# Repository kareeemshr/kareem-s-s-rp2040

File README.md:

# kareem-s-s-rp2040
(small note:there are decoupiling cap's clumped up together cus of space restrictions and no i cant really make the pcb 4 layers because im like 10 bucks away from being over budget)my very own custom devboard that i made...well i made it cus i thought itd be cool as hell and it is,im very proud of myself for making it but nonetheless:

you can use it like a normal raspberry pi pico as far as im aware.

i made it just to learn to how do this type of stuff because i really love the idea of me making my own stuff instead of buying it premade for me so like you could say my dream rn is to build my own custom keyboard but thats for when im actually good at this stuff and also when i get enough money.

**heres the schematic:**

**heres the pcb:**

**heres a render of the board(dont mind the drawings im inlove with sparta and the BOS)**:

|part|ammount|value|link|foot print|
|:----|:-------:|:----:|----|----|
|Capacitor|11|0.1uF|https://jlcpcb.com/partdetail/1877-CL05B104KO5NNNC/C1525|0402|
|Capacitor|2|1uF|https://jlcpcb.com/partdetail/53938-CL05A105KA5NQNC/C52923|0402|
|capacitor|2|10uF|https://jlcpcb.com/partdetail/20411-CL10A106KP8NNNC/C19702|0603|
|capacitor|2|33pF|https://jlcpcb.com/partdetail/1914-0402CG330J500NT/C1562|0402|
|resistor|2|5.1K|https://jlcpcb.com/partdetail/26648-0402WGF5101TCE/C25905|0402|
|resistor|2|27|https://jlcpcb.com/partdetail/25843-0402WGF270JTCE/C25100|0402|
|resistor|2|1K|https://jlcpcb.com/partdetail/12256-0402WGF1001TCE/C11702|0402|
|resistor|1|10K|https://jlcpcb.com/partdetail/26487-0402WGF1002TCE/C25744|0402|
|push button|1||https://jlcpcb.com/partdetail/XUNPU-TS_1088AR02016/C720477|SW_Push_SPST_NO_Alps_SKRK|
|usb-c input|1||https://jlcpcb.com/partdetail/Korean_HropartsElec-TYPE_C_31_M12/C165948|USB_C_Receptacle_HRO_TYPE-C-31-M-12|
|MCU(rp 2040)|1||https://jlcpcb.com/partdetail/RaspberryPi-RP2040/C2040|QFN-56-1EP_7x7mm_P0.4mm_EP3.2x3.2mm|
|flash mem(W25Q16JVSS)|1|16MB|https://jlcpcb.com/partdetail/WinbondElec-W25Q16JVSSIQ/C131025|SOIC-8_5.3x5.3mm_P1.27mm|
|LOD(MCP1700x-330xxTT)|1|5.5V inpt 3.3V outp|https://jlcpcb.com/partdetail/MSKSEMI-MCP1700T_3302E_TT_MS/C20627188|SOT-23|
|crystal|1|12MHZ|https://jlcpcb.com/partdetail/NDK-NX3225GA_12MHZ_STD_CRG2/C481407|Crystal_SMD_3225-4Pin_3.2x2.5mm|

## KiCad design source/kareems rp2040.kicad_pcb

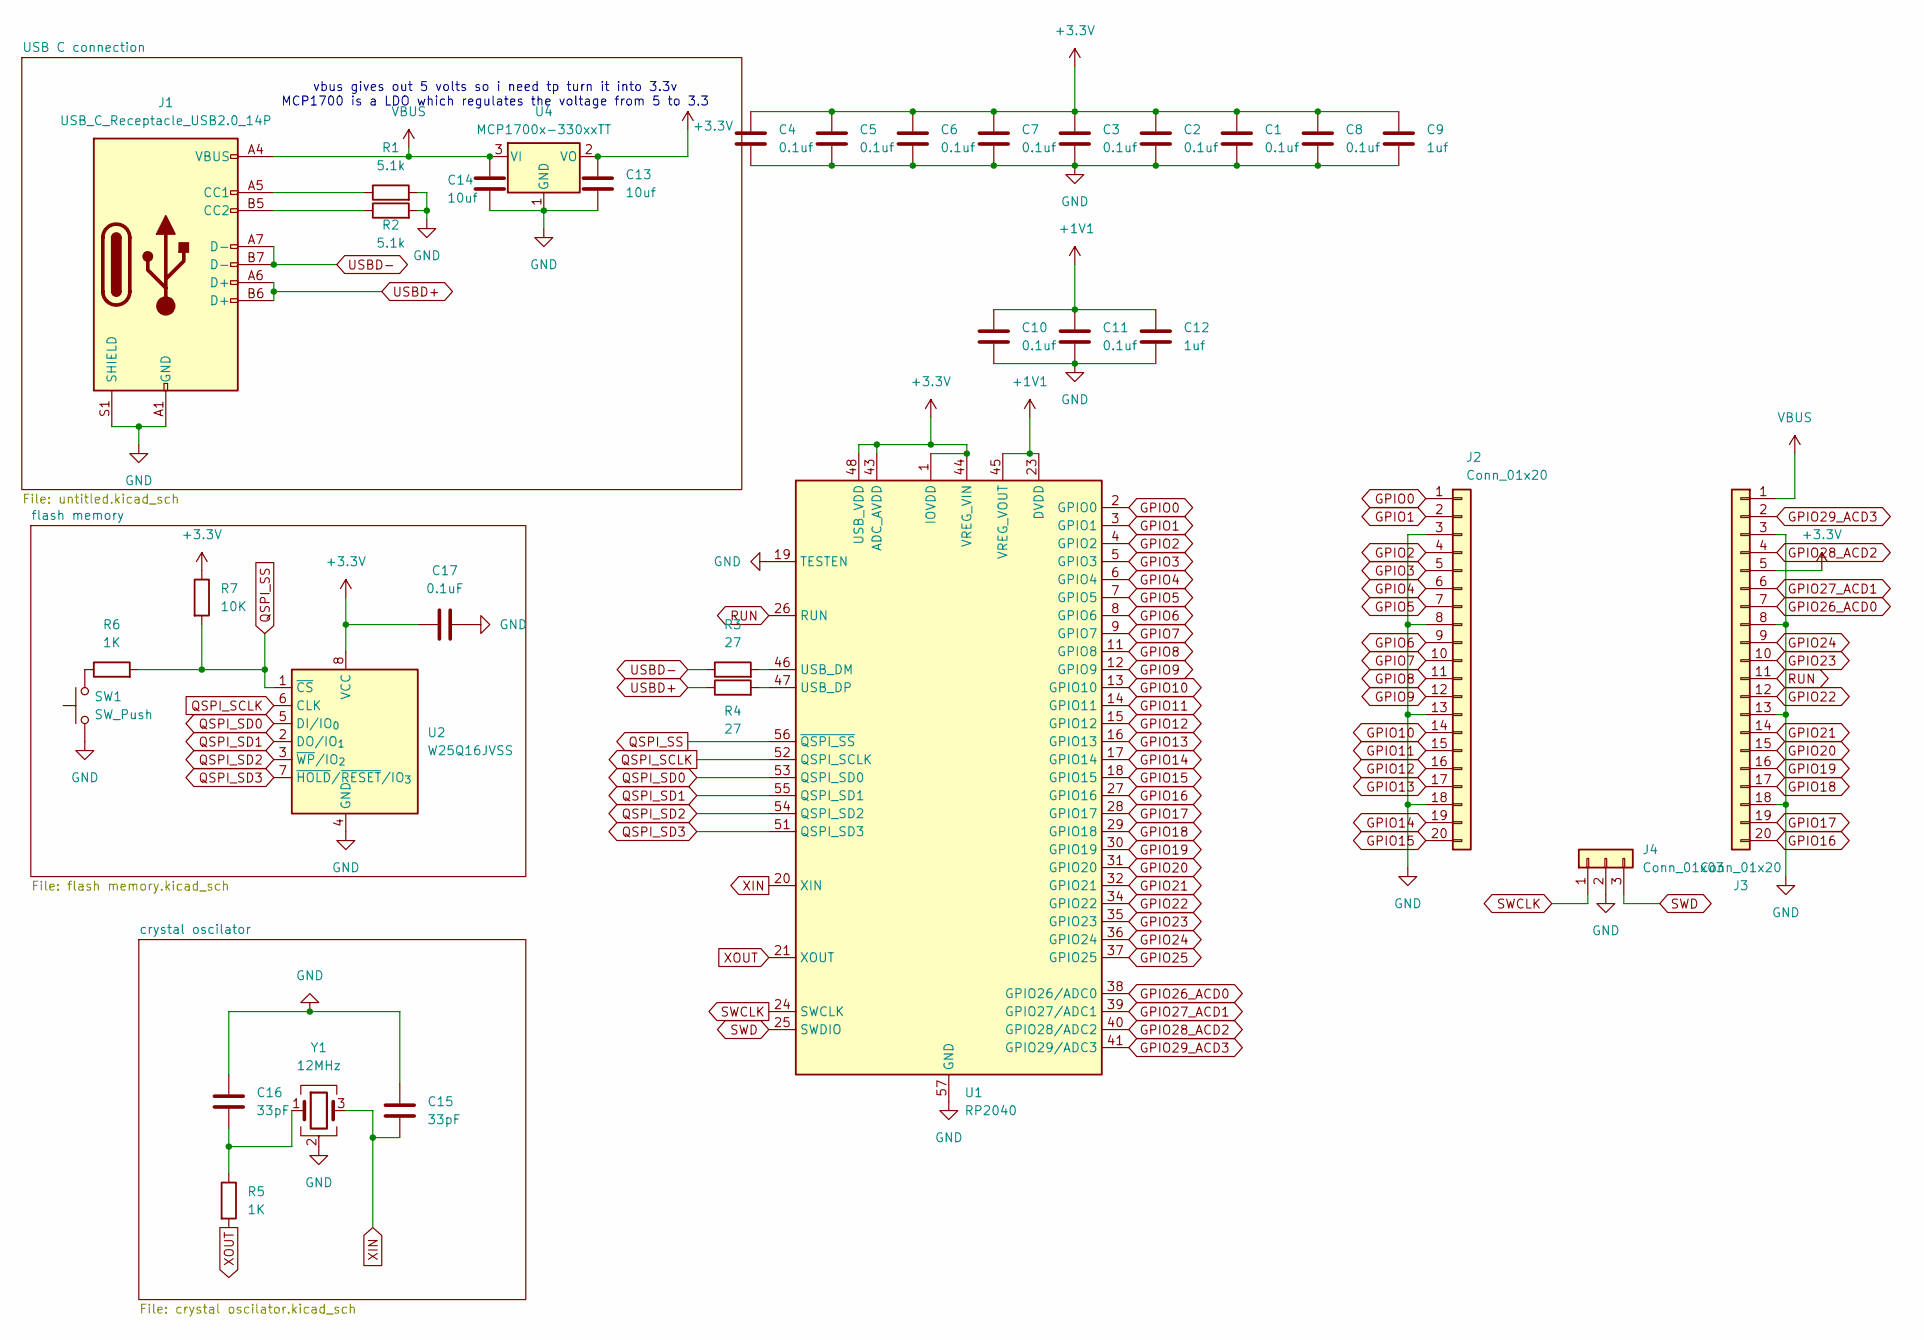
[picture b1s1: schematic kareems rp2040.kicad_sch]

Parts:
C1, C2, C3, C4, C5, C6, C7, C8, C10, C11: 0.1uf; C_0402_1005Metric
C9, C12: 1uf; C_0402_1005Metric
C13, C14: 10uf; C_0603_1608Metric
C15, C16: 33pF; C_0402_1005Metric
C17: 0.1uF; C_0402_1005Metric
J1: USB_C_Receptacle_USB2.0_14P; USB_C_Receptacle_HRO_TYPE-C-31-M-12
J2, J3: Conn_01x20; PinHeader_1x20_P2.54mm_Vertical
J4: Conn_01x03; PinHeader_1x03_P2.54mm_Vertical
R1, R2: 5.1k; R_0402_1005Metric
R3, R4: 27; R_0402_1005Metric
R5, R6: 1K; R_0402_1005Metric
R7: 10K; R_0402_1005Metric
SW1: SW_Push; SW_Push_SPST_NO_Alps_SKRK
U1: RP2040; QFN-56-1EP_7x7mm_P0.4mm_EP3.2x3.2mm
U2: W25Q16JVSS; SOIC-8_5.3x5.3mm_P1.27mm
U4: MCP1700x-330xxTT; SOT-23
Y1: 12MHz; Crystal_SMD_3225-4Pin_3.2x2.5mm

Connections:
+1V1: C10.1, C11.1, C12.1, U1.23 (DVDD), U1.45 (VREG_VOUT), U1.50 (DVDD)
+3.3V: C1.1, C2.1, C3.1, C4.1, C5.1, C6.1, C7.1, C8.1, C9.1, C13.1, C17.1, J3.5, R7.1, U1.1 (IOVDD), U1.10 (IOVDD), U1.22 (IOVDD), U1.33 (IOVDD), U1.42 (IOVDD), U1.43 (ADC_AVDD), U1.44 (VREG_VIN), U1.48 (USB_VDD), U1.49 (IOVDD), U2.8 (VCC), U4.2 (VO)
GND: C1.2, C2.2, C3.2, C4.2, C5.2, C6.2, C7.2, C8.2, C9.2, C10.2, C11.2, C12.2, C13.2, C14.2, C15.2, C16.2, C17.2, J1.A1 (GND), J1.A12 (GND), J1.B1 (GND), J1.B12 (GND), J1.S1 (SHIELD), J2.3, J2.8, J2.13, J2.18, J3.3, J3.8, J3.13, J3.18, J4.2, R1.2, R2.2, SW1.1, U1.19 (TESTEN), U1.57 (GND), U2.4 (GND), U4.1 (GND), Y1.2 (G), Y1.4 (G)
GPIO0: J2.1, U1.2 (GPIO0)
GPIO1: J2.2, U1.3 (GPIO1)
GPIO2: J2.4, U1.4 (GPIO2)
GPIO3: J2.5, U1.5 (GPIO3)
GPIO4: J2.6, U1.6 (GPIO4)
GPIO5: J2.7, U1.7 (GPIO5)
GPIO6: J2.9, U1.8 (GPIO6)
GPIO7: J2.10, U1.9 (GPIO7)
GPIO8: J2.11, U1.11 (GPIO8)
GPIO9: J2.12, U1.12 (GPIO9)
GPIO10: J2.14, U1.13 (GPIO10)
GPIO11: J2.15, U1.14 (GPIO11)
GPIO12: J2.16, U1.15 (GPIO12)
GPIO13: J2.17, U1.16 (GPIO13)
GPIO14: J2.19, U1.17 (GPIO14)
GPIO15: J2.20, U1.18 (GPIO15)
GPIO16: J3.20, U1.27 (GPIO16)
GPIO17: J3.19, U1.28 (GPIO17)
GPIO18: J3.17, U1.29 (GPIO18)
GPIO19: J3.16, U1.30 (GPIO19)
GPIO20: J3.15, U1.31 (GPIO20)
GPIO21: J3.14, U1.32 (GPIO21)
GPIO22: J3.12, U1.34 (GPIO22)
GPIO23: J3.10, U1.35 (GPIO23)
GPIO24: J3.9, U1.36 (GPIO24)
GPIO25: U1.37 (GPIO25)
GPIO26_ACD0: J3.7, U1.38 (GPIO26/ADC0)
GPIO27_ACD1: J3.6, U1.39 (GPIO27/ADC1)
GPIO28_ACD2: J3.4, U1.40 (GPIO28/ADC2)
GPIO29_ACD3: J3.2, U1.41 (GPIO29/ADC3)
unnamed: C16.1, R5.1, Y1.1
unnamed: J1.A5 (CC1), R1.1
unnamed: J1.B5 (CC2), R2.1
unnamed: R6.1, SW1.2
unnamed 37: R3.2, U1.46 (USB_DM); also elsewhere on the board
unnamed 38: R4.2, U1.47 (USB_DP); also elsewhere on the board
QSPI_SCLK: U1.52 (QSPI_SCLK), U2.6 (CLK)
QSPI_SD0: U1.53 (QSPI_SD0), U2.5 (DI/IO_{0})
QSPI_SD1: U1.55 (QSPI_SD1), U2.2 (DO/IO_{1})
QSPI_SD2: U1.54 (QSPI_SD2), U2.3 (~WP/IO_{2})
QSPI_SD3: U1.51 (QSPI_SD3), U2.7 (~HOLD/~RESET/IO_{3})
QSPI_SS: R6.2, R7.2, U1.56 (~QSPI_SS), U2.1 (~CS)
RUN: J3.11, U1.26 (RUN)
SWCLK: J4.1, U1.24 (SWCLK)
SWD: J4.3, U1.25 (SWDIO)
USBD+: J1.A6 (D+), J1.B6 (D+), R4.1; also elsewhere on the board
USBD-: J1.A7 (D-), J1.B7 (D-), R3.1; also elsewhere on the board
VBUS: C14.1, J1.A4 (VBUS), J1.A9 (VBUS), J1.B4 (VBUS), J1.B9 (VBUS), J3.1, U4.3 (VI)
XIN: C15.1, U1.20 (XIN), Y1.3
XOUT: R5.2, U1.21 (XOUT)

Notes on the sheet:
vbus gives out 5 volts so i need tp turn it into 3.3v MCP1700 is a LDO which regulates the voltage from 5 to 3.3

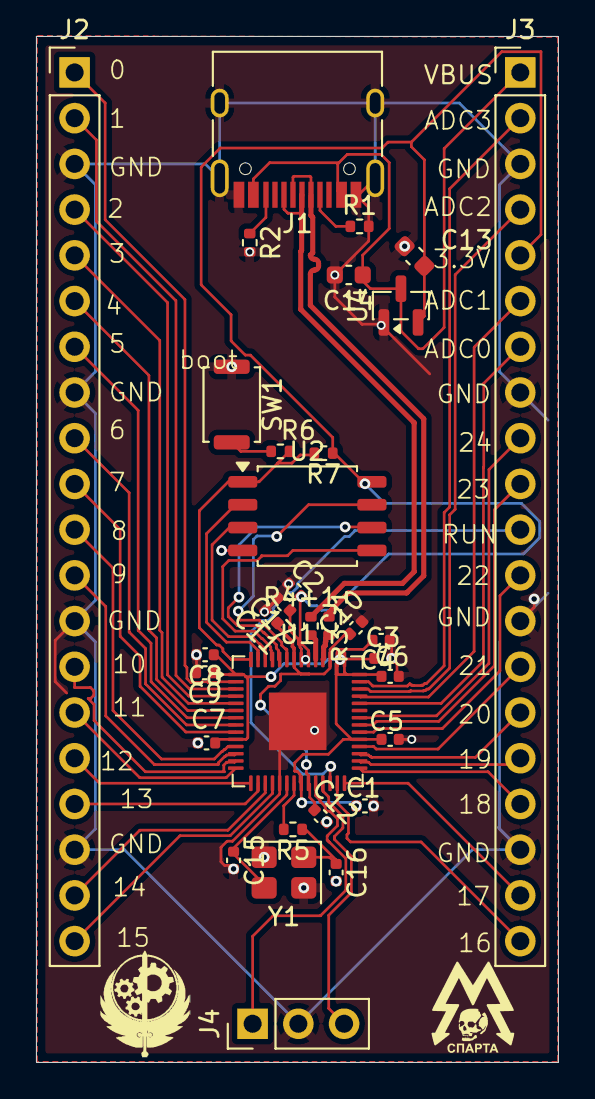
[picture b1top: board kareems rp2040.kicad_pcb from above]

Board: 2 copper layers, 29.0 x 57.0 mm, 33 parts (0 on the bottom side), 52 nets.

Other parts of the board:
R3-1, R4+1: 27; R_0402_1005Metric

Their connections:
unnamed 37: R3-1.2; also elsewhere on the board
unnamed 38: R4+1.2; also elsewhere on the board
USBD+: R4+1.1; also elsewhere on the board
USBD-: R3-1.1; also elsewhere on the board

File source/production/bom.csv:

Designator,Footprint,Quantity,Value,LCSC Part #
"C1, C10, C11, C17, C2, C3, C4, C5, C6, C7, C8",0402,11,0.1uf,
"C12, C9",0402,2,1uf,
"C13, C14",0603,2,10uf,
"C15, C16",0402,2,33pF,
J1,USB_C_Receptacle_HRO_TYPE-C-31-M-12,1,USB_C_Receptacle_USB2.0_14P,
"J2, J3",PinHeader_1x20_P2.54mm_Vertical,2,Conn_01x20,
J4,PinHeader_1x03_P2.54mm_Vertical,1,Conn_01x03,
"R1, R2",0402,2,5.1k,
"R3, R4",0402,2,27,
"R5, R6",0402,2,1K,
R7,0402,1,10K,
SW1,SW_Push_SPST_NO_Alps_SKRK,1,SW_Push,
U1,QFN-56-1EP_7x7mm_P0.4mm_EP3.2x3.2mm,1,RP2040,
U2,SOIC-8_5.3x5.3mm_P1.27mm,1,W25Q16JVSS,
U4,SOT-23,1,MCP1700x-330xxTT,
Y1,Crystal_SMD_3225-4Pin_3.2x2.5mm,1,12MHz,

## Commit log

2026-03-02 Enhance README with project details and components
    Expanded the README to include more details about the custom devboard, including personal insights, usage, and component links.
2026-03-02 added project files
2026-03-03 fixed the location of prodcution file
2026-03-03 Enhance README formatting and add parts list
    Formatted schematic, PCB, and render sections for clarity. Added a detailed parts list with links and specifications.
2026-03-03 lele
2026-03-04 fixed the name of the source file
2026-03-05 Update schematic and PCB images in README
2026-03-17 Update README with new PCB image and board render
    Added additional PCB image and updated board render.
2026-03-18 Update README with clearer project description
    Revised the introduction for clarity and conciseness.
2026-03-22 eeee
2026-03-25 Update PCB and render images in README
